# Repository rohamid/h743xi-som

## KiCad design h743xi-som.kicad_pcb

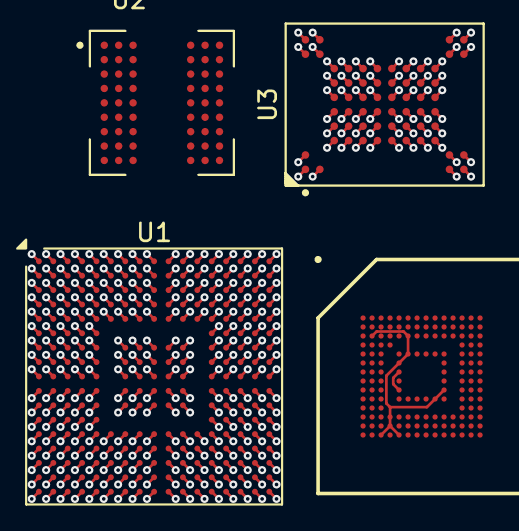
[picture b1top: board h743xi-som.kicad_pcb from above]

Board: 2 copper layers, 4 parts (0 on the bottom side), 3 nets.

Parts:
U1: STM32H743XIH6; TFBGA-265_14x14mm_Layout17x17_P0.8mm
U2: IS42S16160J-6BLI; BGA54C80P9X9_800X800X120
U3: MX30LF1G18AC-XKI; BGA63C80P10X12_900X1100X100N
U4: KLM8G1GETF-B041; BGA153C50P14X14_1150X1300X80

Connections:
+3V3: U1.A6 (VDDLDO), U1.C17 (VDDLDO), U1.E6 (VDD), U1.E9 (VDD), U1.E11 (VDD), U1.F5 (VDD), U1.F17 (VDD33USB), U1.G5 (VDD), U1.G13 (VDD), U1.G17 (VDD50USB), U1.H5 (VDD), U1.H13 (VDD), U1.J13 (VDD), U1.K5 (VDD), U1.K13 (VDD), U1.L1 (VDDA), U1.L5 (VDD), U1.L13 (VDD), U1.M5 (VDD), U1.M13 (VDD), U1.N7 (VDD), U1.N8 (VDD), U1.N10 (VDD), U1.N11 (VDD), U1.N12 (VDD), U1.P17 (VDD), U1.U12 (VDDLDO), U2.A7 (VDDQ), U2.A9 (VDD), U2.B3 (VDDQ), U2.C7 (VDDQ), U2.D3 (VDDQ), U2.E7 (VDD), U2.J9 (VDD), U3.D3 (VCC*), U3.G4 (VCC*), U3.H8 (VCC), U3.J6 (VCC), U4.C2 (VDDI), U4.C6 (VCCQ), U4.E6 (VCC), U4.F5 (VCC), U4.J10 (VCC), U4.K9 (VCC), U4.M4 (VCCQ), U4.N4 (VCCQ), U4.P3 (VCCQ), U4.P5 (VCCQ)
GND: U1.A1 (VSS), U1.A17 (VSS), U1.B2 (VSS), U1.B6 (VSS), U1.C10 (VSS), U1.C13 (VSS), U1.C16 (VSS), U1.F2 (VSS), U1.G7 (VSS), U1.G8 (VSS), U1.G9 (VSS), U1.G10 (VSS), U1.G11 (VSS), U1.G16 (VSS), U1.H7 (VSS), U1.H8 (VSS), U1.H9 (VSS), U1.H10 (VSS), U1.H11 (VSS), U1.J3 (VSS), U1.J7 (VSS), U1.J8 (VSS), U1.J9 (VSS), U1.J10 (VSS), U1.J11 (VSS), U1.J16 (VSS), U1.J17 (VSS), U1.K7 (VSS), U1.K8 (VSS), U1.K9 (VSS), U1.K10 (VSS), U1.K11 (VSS), U1.K15 (VSS), U1.L7 (VSS), U1.L8 (VSS), U1.L9 (VSS), U1.L10 (VSS), U1.L11 (VSS), U1.L15 (VSS), U1.M15 (VSS), U1.N16 (VSS), U1.P1 (VSSA), U1.R4 (VSS), U1.R8 (VSS), U1.T12 (VSS), U1.U1 (VSS), U1.U17 (VSS), U2.A1 (VSS), U2.A3 (VSSQ), U2.B7 (VSSQ), U2.C3 (VSSQ), U2.D7 (VSSQ), U2.E3 (VSS), U2.J1 (VSS), U3.C5 (VSS), U3.F7 (VSS*), U3.K3 (VSS), U3.K8 (VSS), U4.A6 (VSS), U4.C4 (VSS), U4.E7 (VSS), U4.G5 (VSS), U4.H10 (VSS), U4.J5 (VSS), U4.K8 (VSS), U4.N2 (VSS), U4.N5 (VSS), U4.P4 (VSS), U4.P6 (VSS)
unnamed: U1.A7 (VCAP), U1.D17 (VCAP)

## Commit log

2024-05-08 Added my own memory libs, because snapeda or octopart gave me wrong pin library
2024-05-27 Added octospi flash lib
